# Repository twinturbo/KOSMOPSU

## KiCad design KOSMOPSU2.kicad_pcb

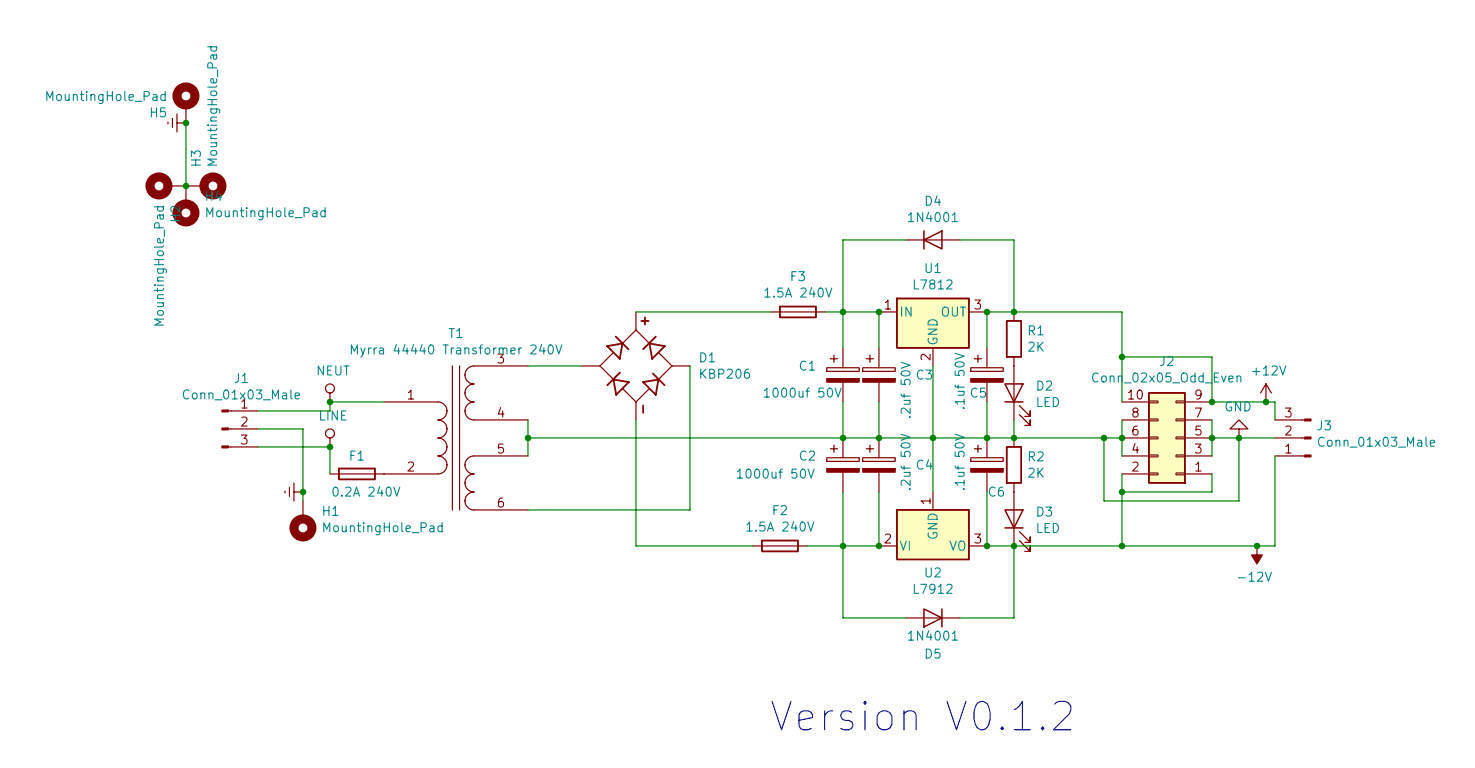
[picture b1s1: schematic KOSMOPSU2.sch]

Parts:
C1, C2: 1000uf 50V; CP_Radial_D16.0mm_P7.50mm
C3, C4: .2uf 50V; CP_Radial_D6.3mm_P2.50mm
C5, C6: .1uf 50V; CP_Radial_D6.3mm_P2.50mm
D1: KBP206; SIP380W81P386L1470H1270Q4
D2, D3: LED; LED_D5.0mm
D4, D5: 1N4001; D_A-405_P10.16mm_Horizontal
F1: 0.2A 240V; googiefuse
F2, F3: 1.5A 240V; PCB-20MM-FUSE-HOLDER
H1, H2, H3, H4, H5: MountingHole_Pad; MountingHole_2.7mm_M2.5_DIN965_Pad
J1: Conn_01x03_Male; Molex_KK-396_A-41791-0003_1x03_P3.96mm_Vertical
J2: Conn_02x05_Odd_Even; IDC-Header_2x05_P2.54mm_Vertical
J3: Conn_01x03_Male; Molex_KK-254_AE-6410-03A_1x03_P2.54mm_Vertical
R1, R2: 2K; R_Axial_DIN0207_L6.3mm_D2.5mm_P10.16mm_Horizontal
T1: Myrra 44440 Transformer 240V; Transformer_Myrra_44440
U1: L7812; TO-220-3_Vertical
U2: L7912; TO-220-3_Vertical

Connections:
+12V: C5.1, D4.2 (A), J2.9, J2.10, J3.3, R1.1, U1.3 (OUT)
-12V: C6.2, D3.1 (K), D5.1 (K), J2.1, J2.2, J3.1, U2.3 (VO)
Earth: H1.1, H2.1, H3.1, H4.1, H5.1, J1.2
GND: C1.2, C2.1, C3.2, C4.1, C5.2, C6.1, D2.1 (K), J2.3, J2.4, J2.5, J2.6, J2.7, J2.8, J3.2, R2.1, T1.4 (SB), T1.5 (SC), U1.2 (GND), U2.1 (GND)
LINE: F1.2, J1.3
NEUT: J1.1, T1.1 (AA)
unnamed: C1.1, C3.1, D4.1 (K), F3.1, U1.1 (IN)
unnamed: C2.2, C4.2, D5.2 (A), F2.1, U2.2 (VI)
unnamed: D1.1, F3.2
unnamed: D1.2, T1.6 (SD)
unnamed: D1.3, T1.3 (SA)
unnamed: D1.4, F2.2
unnamed: D2.2 (A), R1.2
unnamed: D3.2 (A), R2.2
unnamed: F1.1, T1.2 (AB)

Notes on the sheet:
Version V0.1.2

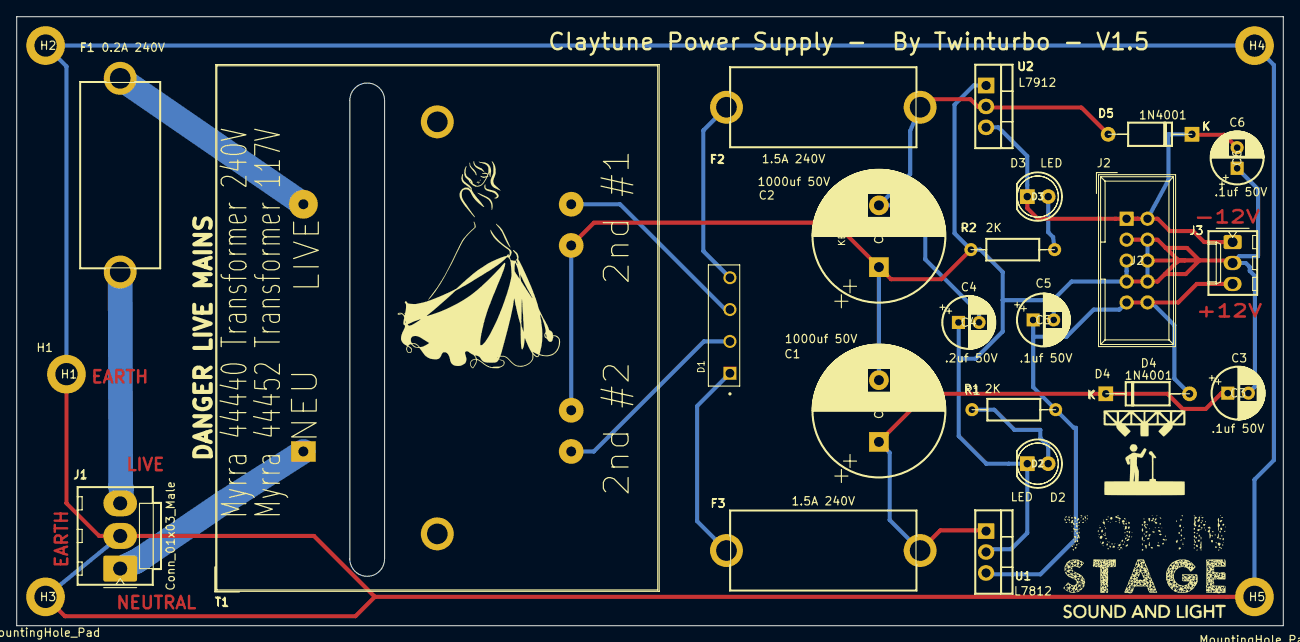
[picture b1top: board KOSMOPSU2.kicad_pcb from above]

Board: 2 copper layers, 153.7 x 73.9 mm, 29 parts (0 on the bottom side), 15 nets.

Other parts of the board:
G1: LOGO; GX-TOBINLOGO
G2: LOGO; GX-F1

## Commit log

2020-10-13 Add files via upload
    Gerber Files for Kosmo PSU
2020-12-04 1st Commit
2020-12-04 cleanup
2020-12-05 autosync
2020-12-05 remsub
2020-12-25 Warning
2020-12-26 Fuse Schematic Update
2020-12-26 C6 Footprint
2020-12-26 Mounting Holes On PCB
2020-12-26 FixLayer
2020-12-26 Value Tidy
2020-12-26 Front Fill removed
2020-12-26 Route Laid Out Manual
2020-12-26 PCB V0.1.4
2020-12-26 Transformer Text
2021-01-03 Cap Update
2022-01-03 -12V header Fix
2022-01-03 -12V header Fix V1.5
2022-02-07 Combined
2025-11-12 MAINSYNC
